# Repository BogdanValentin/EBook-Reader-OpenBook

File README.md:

# Proiect - OpenBook

## Diagrama Bloc

## Pasii de implementare
Am realizat in primul rand schema electrica propusa pe OCW. Apoi am realizat board-ul avand grija prima data sa tai placa dupa dimensiunile precizate. Am pus componentele pe placa incercand sa urmez designul propus. Am pus cele 2 planuri de masa si am rutat firele. Am creat modelele 3D pt placa, baterie si ecran si le-am asamblat in produsul finit.

## Probleme & decizii luate
Senzorul BME688 nu se afla in biblioteca ci BME680 asa ca l-am folosit pe acela. Apar mai multe erori la conectarea firelor GND to GND, am inteles ca mai multi se confrunta cu aceasta problema asa ca am lasat asa. Mufa USB creaza o eroare Board Outline Clearance care, la fel, am inteles ca este una comuna.

## Bill of Materials (BOM)

| Componenta                           | Link de Achizitie           | Datasheet                                                  |
|--------------------------------------|--------------------------------------------|------------------------------------------------------------|
| **USB C connector**                  | [Link](https://ro.mouser.com/ProductDetail/GCT/USB4110-GF-A?qs=KUoIvG%2F9IlYiZvIXQjyJeA%3D%3D&utm_id=6470900573&utm_source=google&utm_medium=cpc&utm_marketing_tactic=emeacorp&gad_source=1&gclid=EAIaIQobChMIw8-8kMWjjAMVcheiAx1TPQ31EAAYAiAAEgLwovD_BwE)                 | [Datasheet](https://ro.mouser.com/datasheet/2/837/GCT_USB4110_Product_Drawing___20k_cycles-3455479.pdf)                                             |
| **ESD Protection**                   | [Link](https://ro.mouser.com/ProductDetail/STMicroelectronics/USBLC6-2SC6Y?qs=gNDSiZmRJS%2FOgDexvXkdow%3D%3D&utm_id=6470900573&utm_source=google&utm_medium=cpc&utm_marketing_tactic=emeacorp&gad_source=1&gclid=EAIaIQobChMI0PCv18SjjAMVl1qRBR1ivRIGEAAYASAAEgKdf_D_BwE)                   | [Datasheet](https://ro.mouser.com/datasheet/2/389/usblc6_2sc6y-1852505.pdf)                                             |
| **LDO Voltage Regulator**            | [Link](https://ro.mouser.com/ProductDetail/Torex-Semiconductor/XC6220A331MR-G?qs=AsjdqWjXhJ8ZSWznL1J0gg%3D%3D&utm_id=6470900573&utm_source=google&utm_medium=cpc&utm_marketing_tactic=emeacorp&gad_source=1&gclid=EAIaIQobChMIyO-xwcSjjAMVwxeiAx0qMg1NEAAYASAAEgLqI_D_BwE)                   | [Datasheet](https://ro.mouser.com/datasheet/2/760/xc6220-3371556.pdf)                                             |
| **SD Card**                          | [Link](https://store.comet.srl.ro/Catalogue/Product/43497/?mark=2)                   | [Datasheet](https://www.attend.com.tw/data/download/file/112A-TAAR-R03.rar)                                             |
| **ESP32 C6**                         | [Link](https://ro.mouser.com/ProductDetail/Espressif-Systems/ESP32-C6?qs=Imq1NPwxi75noDtUpuVuWw%3D%3D&srsltid=AfmBOopGsscg6owTrNYpzSD_A6PeAhrd-8P7Q2gDTU-QmgxBLIUltlA7)                   | [Datasheet](https://ro.mouser.com/datasheet/2/891/esp32_c6_datasheet_en-3304070.pdf)                                             |
| **Li-Po Battery Charging Controller**| [Link](https://ro.mouser.com/ProductDetail/Microchip-Technology/MCP73831-2ATI-MC?qs=hH%252BOa0VZEiCb32ZvHkqhBQ%3D%3D&utm_id=20109199409&utm_source=google&utm_medium=cpc&utm_marketing_tactic=emeacorp&gad_source=1&gclid=EAIaIQobChMIwvChgMajjAMVxRCiAx3PNB47EAAYASAAEgIkZPD_BwE)                   | [Datasheet](https://ro.mouser.com/datasheet/2/268/MCP73831_Family_Data_Sheet_DS20001984H-3441711.pdf)                                             |                                            |
| **E-Paper Drive Circuit**            | [Link](https://ro.mouser.com/ProductDetail/Vishay-Semiconductors/SI1308EDL-T1-GE3?qs=bX1%252BNvsK%2FBramh9tgpOaEw%3D%3D&srsltid=AfmBOop7VB2nsZ4y3AQijBvo753QWrx9w51296dR8UjRlpwp_qg7iivF)                   | [Datasheet](https://www.vishay.com/doc?63399)                                             |
| **E-Paper Display Header**           | [Link](https://ro.mouser.com/ProductDetail/Hirose-Connector/FH34SRJ-24S-0.5SH99?qs=vcbW%252B4%252BSTIpKBl5ap9J8Fw%3D%3D)                   | [Datasheet](https://ro.mouser.com/datasheet/2/185/FH34SRJ_24S_0_5SH_99__CL0580_1255_6_99_2DDrawing_0-1615044.pdf)                                             |
| **EPD Power**                        | [Link](https://ro.mouser.com/ProductDetail/Diodes-Incorporated/DMG2305UX-7?qs=L1DZKBg7t5F%2FNBHrjfxC%252Bg%3D%3D)                   | [Datasheet](https://www.diodes.com/assets/Datasheets/DMG2305UX.pdf)                                             |
| **Environmental Sensor BME688**      | [Link](https://ro.mouser.com/ProductDetail/Bosch-Sensortec/BME688?qs=IS%252B4QmGtzzqQoVDscqwx3A%3D%3D)                   | [Datasheet](https://ro.mouser.com/datasheet/2/783/bst_bme688_fl000-2307034.pdf)                                             |
| **Voltage Supervisor**               | [Link](https://ro.mouser.com/ProductDetail/ROHM-Semiconductor/BD5229G-TR?qs=4kLU8WoGk0vvnhrrYwdszw%3D%3D&srsltid=AfmBOoohF8UhLJmEpguPyHuoa_qfrAg1xACnmLecyTKeAsNQaT9m0ZF5)                   | [Datasheet](https://fscdn.rohm.com/en/products/databook/datasheet/ic/power/voltage_detector/bd52xxg-e.pdf)                                             |
| **Battery Charge Level**             | [Link](https://ro.mouser.com/ProductDetail/Analog-Devices-Maxim-Integrated/MAX17048G+T10?qs=D7PJwyCwLAoGnnn8jEPRBQ%3D%3D&srsltid=AfmBOooZpxDFB0Ef_1d_Z6ZaAY3DUJrF2tjhVNvrkbPhjCJpjsk7k4Qx)                   | [Datasheet](https://ro.mouser.com/datasheet/2/609/MAX17048_MAX17049-3469099.pdf)                                             |
| **RTC Module DS3231SN**              | [Link](https://ro.mouser.com/ProductDetail/Analog-Devices-Maxim-Integrated/DS3231SNTR?qs=1eQvB6Dk1vhN%252BEOl3KU%252Bjw%3D%3D)                   | [Datasheet](https://ro.mouser.com/datasheet/2/609/DS3231-3421123.pdf)                                             |                                            |                                            |
| **SPI ESD Protection Lines**         | [Link](https://ro.mouser.com/ProductDetail/Littelfuse/PGB1010603MR?qs=gu7KAQ731URLg4GSnNNN7Q%3D%3D)                   | [Datasheet](https://www.littelfuse.com/assetdocs/pulseguard-esd-suppressors-pgb1-datasheet?assetguid=8a337998-d54d-466b-be4e-dc5bcd1f9321)                                             |
| **External NORFlash 64MB**           | [Link](https://ro.mouser.com/ProductDetail/Winbond/W25Q512JVEIQ?qs=l7cgNqFNU1jw6svr3at6tA%3D%3D&srsltid=AfmBOooYdTG4zpB4g9XFVQog2As1CX3DBItEO5x_Lv8uh1fPEpwC9MRH)                   | [Datasheet](https://ro.mouser.com/datasheet/2/949/Winbond_W25Q512JV_Datasheet-3240039.pdf)                                             |

---

## 3. Descrierea Functionalitatii Hardware

## Componente Folosite:

1. **USB C connector & ESD protection**  
2. **LDO Voltage Regulator**  
3. **SD card**  
4. **ESP32 C6**  
5. **Li-Po Battery Charging Controller**  
6. **Display Type Selector**  
7. **E-Paper Drive Circuit**  
8. **E-Paper Display Header**  
9. **EPD Power**  
10. **Environmental Sensor BME688**  
11. **Voltage Supervisor + Reset & Boot/IO Button**  
12. **Battery ChargeLevel**  
13. **RTC Module DS3231SN**  
14. **Qwiic/Stemma QT**  
15. **Test Pads**  
16. **SPI ESD Protection Lines**  
17. **External NORFlash 64MB**

---

## 4. ESP32-C6 Pini

| Componenta                          | Pini ESP32       | Rol     |
|-------------------------------------|---------------------|-------------|
| **E-Paper Display**                 | SPI (MISO, MOSI, CLK, CS) | Afisare |
| **BME688**                          | I2C (SDA, SCL)      | Senzor multirol |
| **RTC DS3231SN**                    | I2C (SDA, SCL)      | Ceas / Temporizare  |
| **Li-Po Battery Controller**        | GPIO  | incarcare   |
| **SD Card**                         | SPI (MISO, MOSI, CLK, CS) | Stocare date |
| **Qwiic/Stemma QT**                 | I2C                  | -  |

---

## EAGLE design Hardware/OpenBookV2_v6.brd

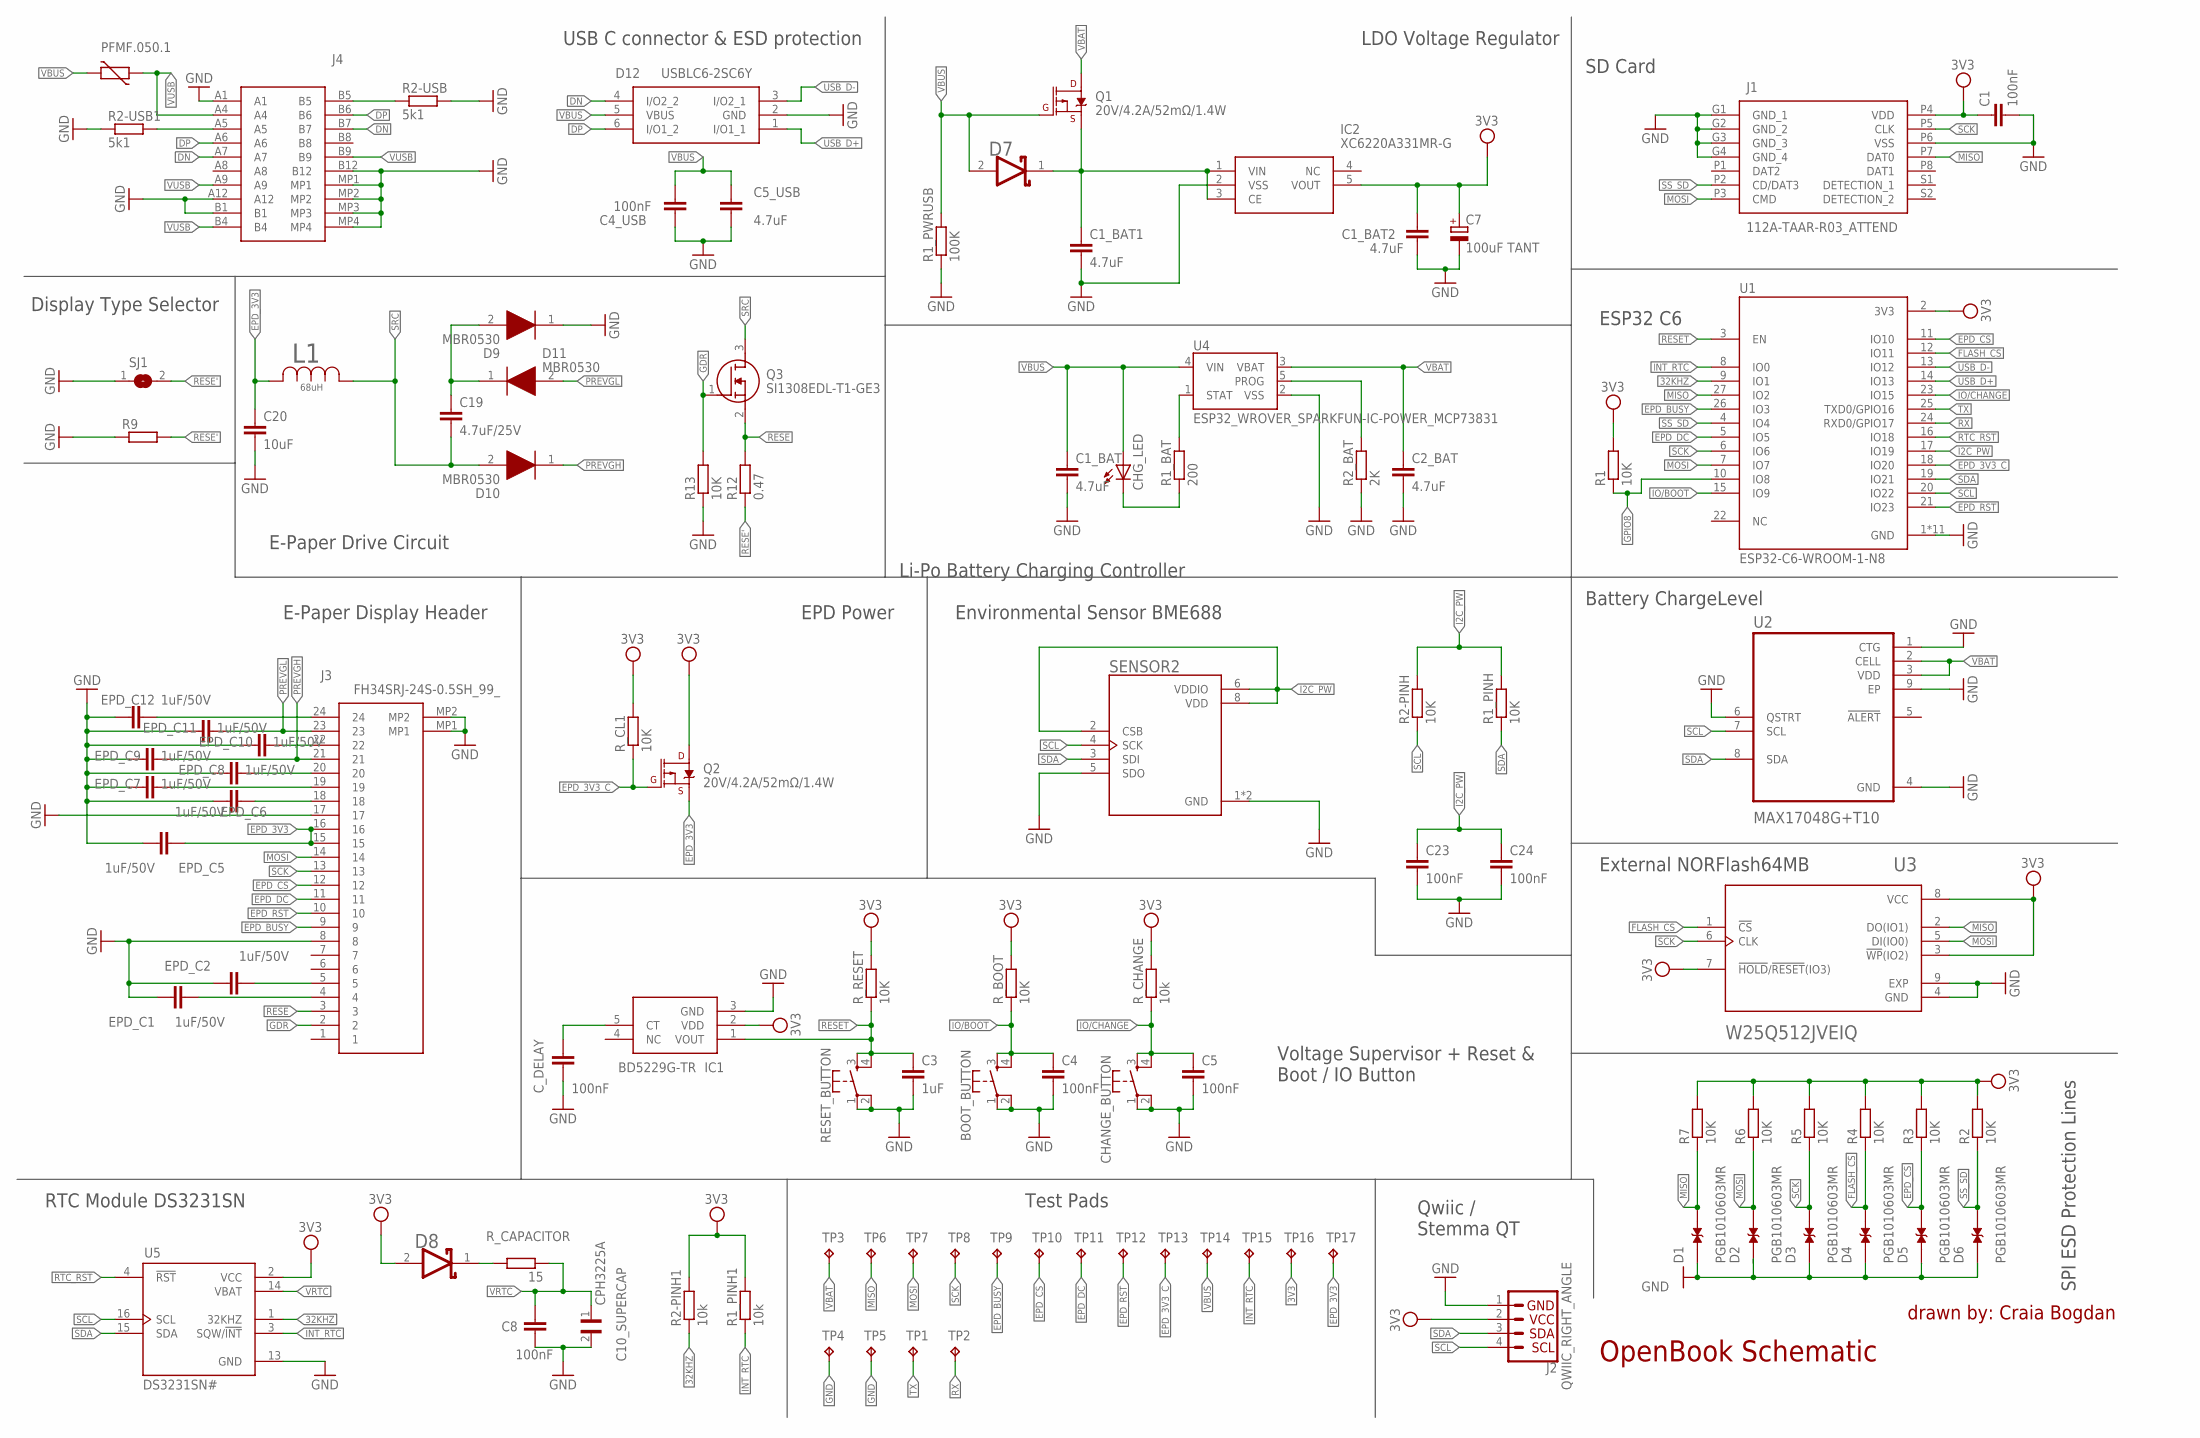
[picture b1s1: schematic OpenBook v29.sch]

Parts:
BOOT_BUTTON: BUTTON_CUSYOMV1; MYBUTTON
C1, C4, C4_USB, C5, C8, C23, C24: 100nF; EAGLE-LTSPICE_C0402
C1_BAT, C1_BAT1, C1_BAT2, C2_BAT, C5_USB: 4.7uF; EAGLE-LTSPICE_C0402
C3: 1uF; EAGLE-LTSPICE_C0402
C7: 100uF TANT; RCL_CT3528
C10_SUPERCAP: CPH3225A; CAPCP3225X100N
C19: 4.7uF/25V; EAGLE-LTSPICE_C0402
C20: 10uF; EAGLE-LTSPICE_C0402
CHANGE_BUTTON: BUTTON_CUSYOMV1; MYBUTTON
CHG_LED: ADAFRUIT_LEDCHIP-LED0603; ADAFRUIT_CHIP-LED0603
C_DELAY: 100nF; EAGLE-LTSPICE_C0402
D1, D2, D3, D4, D5, D6: PGB1010603MR; DIOC1608X36N
D7, D8: ESP32_WROVER_AVX---SD0805S020S1R0_AVX_SD0805S020S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; ESP32_WROVER_AVX---SD0805S020S1R0_AVX_SD0805S020S1R0_0
D9, D10, D11: MBR0530; SOD3716X135N
D12: USBLC6-2SC6Y; SOT95P280X145-6N
EPD_C1, EPD_C2, EPD_C5, EPD_C6, EPD_C7, EPD_C8, EPD_C9, EPD_C10, EPD_C11, EPD_C12: 1uF/50V; EAGLE-LTSPICE_C0402
IC1: BD5229G-TR; SOT95P280X125-5N
IC2: XC6220A331MR-G; SOT95P280X120-5N
J1: 112A-TAAR-R03_ATTEND; 112ATAARR03ATTEND
J2: QWIIC_RIGHT_ANGLE; JST04_1MM_RA
J3: FH34SRJ-24S-0.5SH_99_; FH34SRJ24S05SH99
J4: SAMACSYS_PARTS_USB4110-GF-A; SAMACSYS_PARTS_USB4110GFA
L1: 68uH; IND_4828-WE-TPC_WRE
PFMF.050.1: ESP32C6_VARISTORCN1812; ESP32C6_VARISTOR_CT/CN1812
Q1, Q2: 20V/4.2A/52mΩ/1.4W; ESP32_WROVER_SPARKFUN-DISCRETESEMI_SOT23-3
Q3: SI1308EDL-T1-GE3; SOT65P210X110-3N
R1, R1_PINH, R2, R2-PINH, R3, R4, R5, R6, R7, R13: 10K; ESP32_WROVER_EAGLE-LTSPICE_R0402
R1_BAT: 200; ESP32_WROVER_EAGLE-LTSPICE_R0402
R1_PINH1, R2-PINH1: 10k; ESP32_WROVER_EAGLE-LTSPICE_R0402
R1_PWRUSB: 100K; ESP32_WROVER_EAGLE-LTSPICE_R0402
R2-USB, R2-USB1: 5k1; ESP32_WROVER_EAGLE-LTSPICE_R0402
R2_BAT: 2K; ESP32_WROVER_EAGLE-LTSPICE_R0402
R9: ESP32_WROVER_EAGLE-LTSPICE_RR0402; ESP32_WROVER_EAGLE-LTSPICE_R0402
R12: 0.47; ESP32_WROVER_EAGLE-LTSPICE_R0402
RESET_BUTTON: BUTTON_CUSYOMV1; MYBUTTON
R_BOOT: 10K; ESP32_WROVER_EAGLE-LTSPICE_R0402
R_CAPACITOR: 15; ESP32_WROVER_EAGLE-LTSPICE_R0402
R_CHANGE: 10k; ESP32_WROVER_EAGLE-LTSPICE_R0402
R_CL1: 10K; ESP32_WROVER_EAGLE-LTSPICE_R0402
R_RESET: 10K; ESP32_WROVER_EAGLE-LTSPICE_R0402
SENSOR2: ESP32_WROVER_BME680_BME680; ESP32_WROVER_BME680_PSON80P300X300X100-8N
SJ1: SJ
TP1, TP2, TP3, TP4, TP5, TP6, TP7, TP8, TP9, TP10, TP11, TP12, TP13, TP14, TP15, TP16, TP17: TPTP20R; TP20R
U1: ESP32-C6-WROOM-1-N8; XCVR_ESP32-C6-WROOM-1-N8
U2: MAX17048G+T10; SON50P200X200X80-9N
U3: W25Q512JVEIQ; SON127P600X800X80-9N
U4: ESP32_WROVER_SPARKFUN-IC-POWER_MCP73831; ESP32_WROVER_SPARKFUN-IC-POWER_SOT23-5
U5: DS3231SN#; SOIC127P1032X265-16N

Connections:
3V3: C1.1, C1_BAT2.1, C7.+, D8.2 (ANODE), IC1.2 (VDD), IC2.5 (VOUT), J1.P4 (VDD), J2.2, Q2.3 (D), R1.2, R1_PINH1.2, R2.2, R2-PINH1.2, R3.2, R4.2, R5.2, R6.2, R7.2, R_BOOT.2, R_CHANGE.2, R_CL1.2, R_RESET.2, TP16.TP, U1.2 (3V3), U3.3 (!WP!(IO2)), U3.7 (!HOLD!/!RESET!(IO3)), U3.8 (VCC), U5.2 (VCC)
32KHZ: R2-PINH1.1, U1.9 (IO1), U5.1 (32KHZ)
DN: D12.4 (I/O2_2), J4.A7, J4.B7
DP: D12.6 (I/O1_2), J4.A6, J4.B6
EPD_3V3: C20.1, EPD_C5.2, J3.15, J3.16, L1.2, Q2.2 (S), TP17.TP
EPD_3V3_C: Q2.1 (G), R_CL1.1, TP13.TP, U1.18 (IO20)
EPD_BUSY: J3.9, TP9.TP, U1.26 (IO3)
EPD_CS: D5.2, J3.12, R3.1, TP10.TP, U1.11 (IO10)
EPD_DC: J3.11, TP11.TP, U1.5 (IO5)
EPD_RST: J3.10, TP12.TP, U1.21 (IO23)
FLASH_CS: D4.2, R4.1, U1.12 (IO11), U3.1 (!CS)
GDR: J3.2, Q3.1 (G), R13.2
GND: BOOT_BUTTON.1, BOOT_BUTTON.2, C1.2, C1_BAT.2, C1_BAT1.2, C1_BAT2.2, C2_BAT.2, C3.2, C4.2, C4_USB.2, C5.2, C5_USB.2, C7.-, C8.2, C10_SUPERCAP.2, C20.2, C23.2, C24.2, CHANGE_BUTTON.1, CHANGE_BUTTON.2, C_DELAY.2, D1.1, D2.1, D3.1, D4.1, D5.1, D6.1, D9.1 (K), D12.2 (GND), EPD_C1.1, EPD_C2.1, EPD_C5.1, EPD_C6.1, EPD_C7.1, EPD_C8.1, EPD_C9.1, EPD_C10.1, EPD_C11.1, EPD_C12.1, IC1.3 (GND), IC2.2 (VSS), J1.G1 (GND_1), J1.G2 (GND_2), J1.G3 (GND_3), J1.G4 (GND_4), J1.P6 (VSS), J2.1, J3.8, J3.17, J3.MP1, J3.MP2, J4.A1, J4.A12, J4.B1, J4.B12, J4.MP1, J4.MP2, J4.MP3, J4.MP4, R1_PWRUSB.1, R2-USB.2, R2-USB1.1, R2_BAT.1, R9.1, R13.1, RESET_BUTTON.1, RESET_BUTTON.2, SENSOR2.1 (GND), SENSOR2.5 (SDO), SENSOR2.7 (GND), SJ1.1, TP4.TP, TP5.TP, U1.1 (GND), U1.28 (GND), U1.29_1 (GND), U1.29_2 (GND), U1.29_3 (GND), U1.29_4 (GND), U1.29_5 (GND), U1.29_6 (GND), U1.29_7 (GND), U1.29_8 (GND), U1.29_9 (GND), U2.1 (CTG), U2.4 (GND), U2.6 (QSTRT), U2.9 (EP), U3.4 (GND), U3.9 (EXP), U4.2 (VSS), U5.13 (GND)
GPIO8: R1.1, U1.10 (IO8)
I2C_PW: C23.1, C24.1, R1_PINH.2, R2-PINH.2, SENSOR2.2 (CSB), SENSOR2.6 (VDDIO), SENSOR2.8 (VDD), U1.17 (IO19)
INT_RTC: R1_PINH1.1, TP15.TP, U1.8 (IO0), U5.3 (SQW/!INT)
IO/BOOT: BOOT_BUTTON.3, BOOT_BUTTON.4, C4.1, R_BOOT.1, U1.15 (IO9)
IO/CHANGE: C5.1, CHANGE_BUTTON.3, CHANGE_BUTTON.4, R_CHANGE.1, U1.23 (IO15)
MISO: D1.2, J1.P7 (DAT0), R7.1, TP6.TP, U1.27 (IO2), U3.2 (DO(IO1))
MOSI: D2.2, J1.P3 (CMD), J3.14, R6.1, TP7.TP, U1.7 (IO7), U3.5 (DI(IO0))
unnamed: C_DELAY.1, IC1.5 (CT)
unnamed: C1_BAT1.1, D7.1 (CATHODE), IC2.1 (VIN), IC2.3 (CE), Q1.2 (S)
unnamed: CHG_LED.C, R1_BAT.1
unnamed: R1_BAT.2, U4.1 (STAT)
unnamed: R2_BAT.2, U4.5 (PROG)
unnamed: D8.1 (CATHODE), R_CAPACITOR.1
unnamed: C19.1, D9.2 (A), D11.1 (K)
unnamed: J4.A5, R2-USB1.2
unnamed: J4.B5, R2-USB.1
unnamed: EPD_C2.2, J3.5
unnamed: EPD_C1.2, J3.4
unnamed: EPD_C6.2, J3.18
unnamed: EPD_C8.2, J3.20
unnamed: EPD_C10.2, J3.22
unnamed: EPD_C7.2, J3.19
unnamed: EPD_C12.2, J3.24
PREVGH: D10.1 (K), EPD_C9.2, J3.21
PREVGL: D11.2 (A), EPD_C11.2, J3.23
RESE: J3.3, Q3.2 (S), R12.2
RESE': R9.2, R12.1, SJ1.2
RESET: C3.1, IC1.1 (VOUT), RESET_BUTTON.3, RESET_BUTTON.4, R_RESET.1, U1.3 (EN)
RTC_RST: U1.16 (IO18), U5.4 (!RST)
RX: TP2.TP, U1.24 (RXD0/GPIO17)
SCK: D3.2, J1.P5 (CLK), J3.13, R5.1, TP8.TP, U1.6 (IO6), U3.6 (CLK)
SCL: J2.4, R2-PINH.1, SENSOR2.4 (SCK), U1.20 (IO22), U2.7 (SCL), U5.16 (SCL)
SDA: J2.3, R1_PINH.1, SENSOR2.3 (SDI), U1.19 (IO21), U2.8 (SDA), U5.15 (SDA)
SRC: C19.2, D10.2 (A), L1.1, Q3.3 (D)
SS_SD: D6.2, J1.P2 (CD/DAT3), R2.1, U1.4 (IO4)
TX: TP1.TP, U1.25 (TXD0/GPIO16)
USB_D+: D12.1 (I/O1_1), U1.14 (IO13)
USB_D-: D12.3 (I/O2_1), U1.13 (IO12)
VBAT: C2_BAT.1, Q1.3 (D), TP3.TP, U2.2 (CELL), U2.3 (VDD), U4.3 (VBAT)
VBUS: C1_BAT.1, C4_USB.1, C5_USB.1, CHG_LED.A, D7.2 (ANODE), D12.5 (VBUS), PFMF.050.1.2, Q1.1 (G), R1_PWRUSB.2, TP14.TP, U4.4 (VIN)
VRTC: C8.1, C10_SUPERCAP.1, R_CAPACITOR.2, U5.14 (VBAT)
VUSB: J4.A4, J4.A9, J4.B4, J4.B9, PFMF.050.1.1

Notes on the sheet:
USB C connector & ESD protection
LDO Voltage Regulator
SD Card
ESP32 C6
Li-Po Battery Charging Controller
E-Paper Drive Circuit
Display Type Selector
E-Paper Display Header
EPD Power
Environmental Sensor BME688
Voltage Supervisor + Reset & Boot / IO Button
Battery ChargeLevel
External NORFlash64MB
SPI ESD Protection Lines
Qwiic / Stemma QT
Test Pads
RTC Module DS3231SN
drawn by: Craia Bogdan
OpenBook Schematic

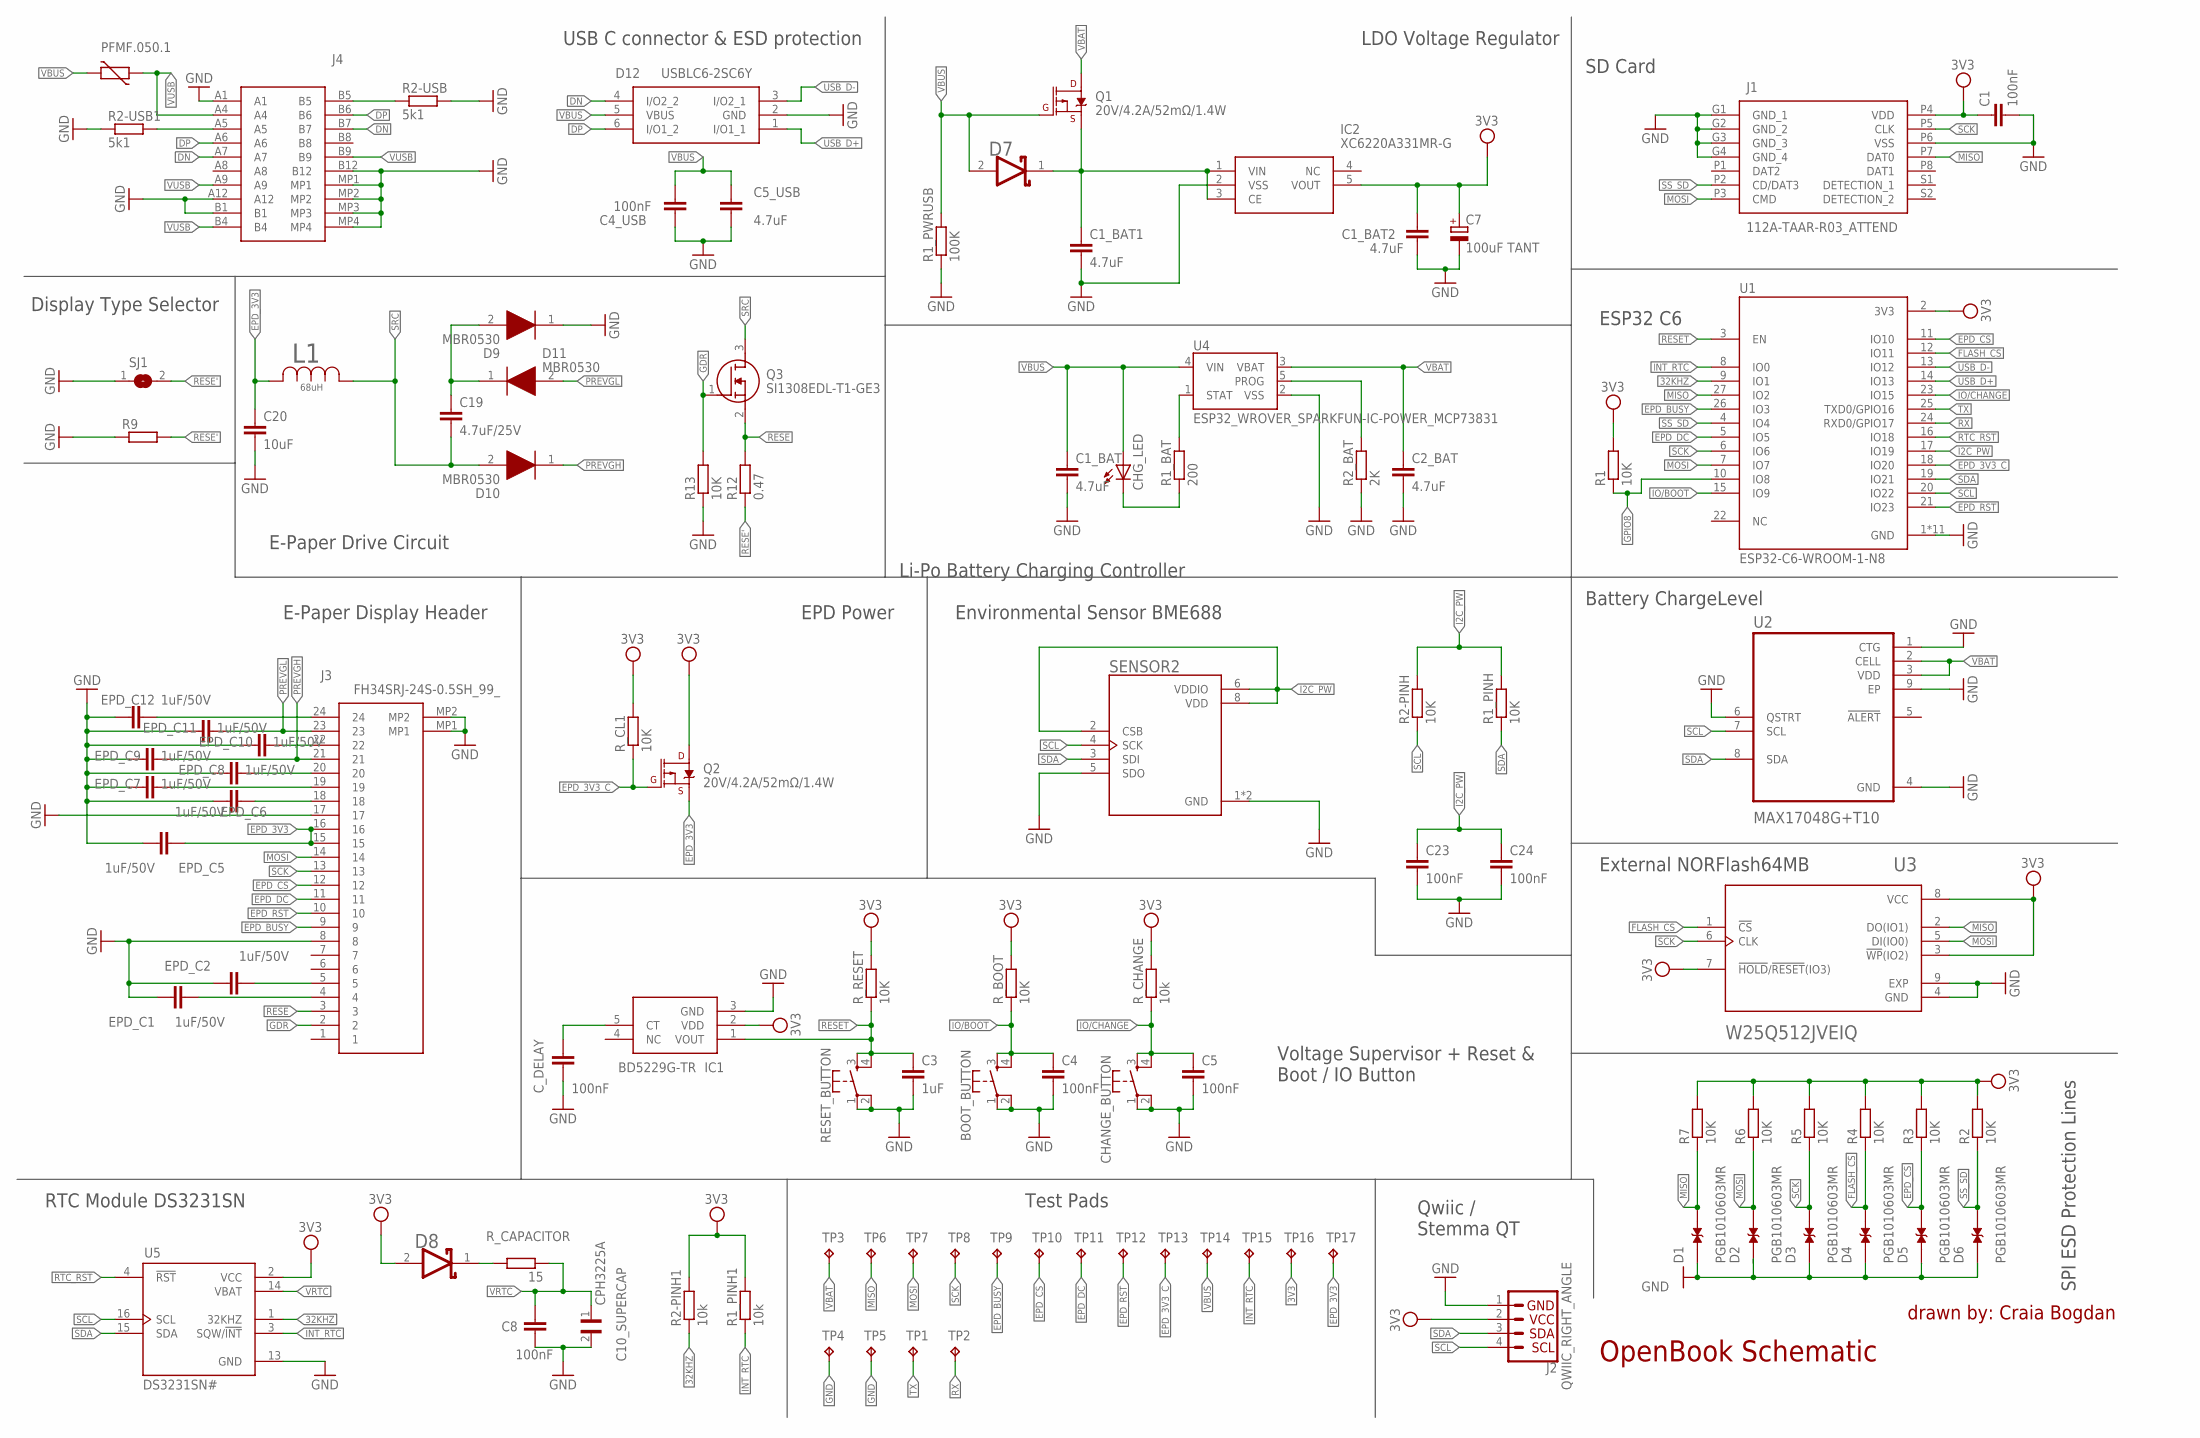
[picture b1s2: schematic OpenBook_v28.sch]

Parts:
BOOT_BUTTON: BUTTON_CUSYOMV1; MYBUTTON
C1, C4, C4_USB, C5, C8, C23, C24: 100nF; EAGLE-LTSPICE_C0402
C1_BAT, C1_BAT1, C1_BAT2, C2_BAT, C5_USB: 4.7uF; EAGLE-LTSPICE_C0402
C3: 1uF; EAGLE-LTSPICE_C0402
C7: 100uF TANT; RCL_CT3528
C10_SUPERCAP: CPH3225A; CAPCP3225X100N
C19: 4.7uF/25V; EAGLE-LTSPICE_C0402
C20: 10uF; EAGLE-LTSPICE_C0402
CHANGE_BUTTON: BUTTON_CUSYOMV1; MYBUTTON
CHG_LED: ADAFRUIT_LEDCHIP-LED0603; ADAFRUIT_CHIP-LED0603
C_DELAY: 100nF; EAGLE-LTSPICE_C0402
D1, D2, D3, D4, D5, D6: PGB1010603MR; DIOC1608X36N
D7, D8: ESP32_WROVER_AVX---SD0805S020S1R0_AVX_SD0805S020S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; ESP32_WROVER_AVX---SD0805S020S1R0_AVX_SD0805S020S1R0_0
D9, D10, D11: MBR0530; SOD3716X135N
D12: USBLC6-2SC6Y; SOT95P280X145-6N
EPD_C1, EPD_C2, EPD_C5, EPD_C6, EPD_C7, EPD_C8, EPD_C9, EPD_C10, EPD_C11, EPD_C12: 1uF/50V; EAGLE-LTSPICE_C0402
IC1: BD5229G-TR; SOT95P280X125-5N
IC2: XC6220A331MR-G; SOT95P280X120-5N
J1: 112A-TAAR-R03_ATTEND; 112ATAARR03ATTEND
J2: QWIIC_RIGHT_ANGLE; JST04_1MM_RA
J3: FH34SRJ-24S-0.5SH_99_; FH34SRJ24S05SH99
J4: SAMACSYS_PARTS_USB4110-GF-A; SAMACSYS_PARTS_USB4110GFA
L1: 68uH; IND_4828-WE-TPC_WRE
PFMF.050.1: ESP32C6_VARISTORCN1812; ESP32C6_VARISTOR_CT/CN1812
Q1, Q2: 20V/4.2A/52mΩ/1.4W; ESP32_WROVER_SPARKFUN-DISCRETESEMI_SOT23-3
Q3: SI1308EDL-T1-GE3; SOT65P210X110-3N
R1, R1_PINH, R2, R2-PINH, R3, R4, R5, R6, R7, R13: 10K; ESP32_WROVER_EAGLE-LTSPICE_R0402
R1_BAT: 200; ESP32_WROVER_EAGLE-LTSPICE_R0402
R1_PINH1, R2-PINH1: 10k; ESP32_WROVER_EAGLE-LTSPICE_R0402
R1_PWRUSB: 100K; ESP32_WROVER_EAGLE-LTSPICE_R0402
R2-USB, R2-USB1: 5k1; ESP32_WROVER_EAGLE-LTSPICE_R0402
R2_BAT: 2K; ESP32_WROVER_EAGLE-LTSPICE_R0402
R9: ESP32_WROVER_EAGLE-LTSPICE_RR0402; ESP32_WROVER_EAGLE-LTSPICE_R0402
R12: 0.47; ESP32_WROVER_EAGLE-LTSPICE_R0402
RESET_BUTTON: BUTTON_CUSYOMV1; MYBUTTON
R_BOOT: 10K; ESP32_WROVER_EAGLE-LTSPICE_R0402
R_CAPACITOR: 15; ESP32_WROVER_EAGLE-LTSPICE_R0402
R_CHANGE: 10k; ESP32_WROVER_EAGLE-LTSPICE_R0402
R_CL1: 10K; ESP32_WROVER_EAGLE-LTSPICE_R0402
R_RESET: 10K; ESP32_WROVER_EAGLE-LTSPICE_R0402
SENSOR2: ESP32_WROVER_BME680_BME680; ESP32_WROVER_BME680_PSON80P300X300X100-8N
SJ1: SJ
TP1, TP2, TP3, TP4, TP5, TP6, TP7, TP8, TP9, TP10, TP11, TP12, TP13, TP14, TP15, TP16, TP17: TPTP20R; TP20R
U1: ESP32-C6-WROOM-1-N8; XCVR_ESP32-C6-WROOM-1-N8
U2: MAX17048G+T10; SON50P200X200X80-9N
U3: W25Q512JVEIQ; SON127P600X800X80-9N
U4: ESP32_WROVER_SPARKFUN-IC-POWER_MCP73831; ESP32_WROVER_SPARKFUN-IC-POWER_SOT23-5
U5: DS3231SN#; SOIC127P1032X265-16N

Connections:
3V3: C1.1, C1_BAT2.1, C7.+, D8.2 (ANODE), IC1.2 (VDD), IC2.5 (VOUT), J1.P4 (VDD), J2.2, Q2.3 (D), R1.2, R1_PINH1.2, R2.2, R2-PINH1.2, R3.2, R4.2, R5.2, R6.2, R7.2, R_BOOT.2, R_CHANGE.2, R_CL1.2, R_RESET.2, TP16.TP, U1.2 (3V3), U3.3 (!WP!(IO2)), U3.7 (!HOLD!/!RESET!(IO3)), U3.8 (VCC), U5.2 (VCC)
32KHZ: R2-PINH1.1, U1.9 (IO1), U5.1 (32KHZ)
DN: D12.4 (I/O2_2), J4.A7, J4.B7
DP: D12.6 (I/O1_2), J4.A6, J4.B6
EPD_3V3: C20.1, EPD_C5.2, J3.15, J3.16, L1.2, Q2.2 (S), TP17.TP
EPD_3V3_C: Q2.1 (G), R_CL1.1, TP13.TP, U1.18 (IO20)
EPD_BUSY: J3.9, TP9.TP, U1.26 (IO3)
EPD_CS: D5.2, J3.12, R3.1, TP10.TP, U1.11 (IO10)
EPD_DC: J3.11, TP11.TP, U1.5 (IO5)
EPD_RST: J3.10, TP12.TP, U1.21 (IO23)
FLASH_CS: D4.2, R4.1, U1.12 (IO11), U3.1 (!CS)
GDR: J3.2, Q3.1 (G), R13.2
GND: BOOT_BUTTON.1, BOOT_BUTTON.2, C1.2, C1_BAT.2, C1_BAT1.2, C1_BAT2.2, C2_BAT.2, C3.2, C4.2, C4_USB.2, C5.2, C5_USB.2, C7.-, C8.2, C10_SUPERCAP.2, C20.2, C23.2, C24.2, CHANGE_BUTTON.1, CHANGE_BUTTON.2, C_DELAY.2, D1.1, D2.1, D3.1, D4.1, D5.1, D6.1, D9.1 (K), D12.2 (GND), EPD_C1.1, EPD_C2.1, EPD_C5.1, EPD_C6.1, EPD_C7.1, EPD_C8.1, EPD_C9.1, EPD_C10.1, EPD_C11.1, EPD_C12.1, IC1.3 (GND), IC2.2 (VSS), J1.G1 (GND_1), J1.G2 (GND_2), J1.G3 (GND_3), J1.G4 (GND_4), J1.P6 (VSS), J2.1, J3.8, J3.17, J3.MP1, J3.MP2, J4.A1, J4.A12, J4.B1, J4.B12, J4.MP1, J4.MP2, J4.MP3, J4.MP4, R1_PWRUSB.1, R2-USB.2, R2-USB1.1, R2_BAT.1, R9.1, R13.1, RESET_BUTTON.1, RESET_BUTTON.2, SENSOR2.1 (GND), SENSOR2.5 (SDO), SENSOR2.7 (GND), SJ1.1, TP4.TP, TP5.TP, U1.1 (GND), U1.28 (GND), U1.29_1 (GND), U1.29_2 (GND), U1.29_3 (GND), U1.29_4 (GND), U1.29_5 (GND), U1.29_6 (GND), U1.29_7 (GND), U1.29_8 (GND), U1.29_9 (GND), U2.1 (CTG), U2.4 (GND), U2.6 (QSTRT), U2.9 (EP), U3.4 (GND), U3.9 (EXP), U4.2 (VSS), U5.13 (GND)
GPIO8: R1.1, U1.10 (IO8)
I2C_PW: C23.1, C24.1, R1_PINH.2, R2-PINH.2, SENSOR2.2 (CSB), SENSOR2.6 (VDDIO), SENSOR2.8 (VDD), U1.17 (IO19)
INT_RTC: R1_PINH1.1, TP15.TP, U1.8 (IO0), U5.3 (SQW/!INT)
IO/BOOT: BOOT_BUTTON.3, BOOT_BUTTON.4, C4.1, R_BOOT.1, U1.15 (IO9)
IO/CHANGE: C5.1, CHANGE_BUTTON.3, CHANGE_BUTTON.4, R_CHANGE.1, U1.23 (IO15)
MISO: D1.2, J1.P7 (DAT0), R7.1, TP6.TP, U1.27 (IO2), U3.2 (DO(IO1))
MOSI: D2.2, J1.P3 (CMD), J3.14, R6.1, TP7.TP, U1.7 (IO7), U3.5 (DI(IO0))
unnamed: C_DELAY.1, IC1.5 (CT)
unnamed: C1_BAT1.1, D7.1 (CATHODE), IC2.1 (VIN), IC2.3 (CE), Q1.2 (S)
unnamed: CHG_LED.C, R1_BAT.1
unnamed: R1_BAT.2, U4.1 (STAT)
unnamed: R2_BAT.2, U4.5 (PROG)
unnamed: D8.1 (CATHODE), R_CAPACITOR.1
unnamed: C19.1, D9.2 (A), D11.1 (K)
unnamed: J4.A5, R2-USB1.2
unnamed: J4.B5, R2-USB.1
unnamed: EPD_C2.2, J3.5
unnamed: EPD_C1.2, J3.4
unnamed: EPD_C6.2, J3.18
unnamed: EPD_C8.2, J3.20
unnamed: EPD_C10.2, J3.22
unnamed: EPD_C7.2, J3.19
unnamed: EPD_C12.2, J3.24
PREVGH: D10.1 (K), EPD_C9.2, J3.21
PREVGL: D11.2 (A), EPD_C11.2, J3.23
RESE: J3.3, Q3.2 (S), R12.2
RESE': R9.2, R12.1, SJ1.2
RESET: C3.1, IC1.1 (VOUT), RESET_BUTTON.3, RESET_BUTTON.4, R_RESET.1, U1.3 (EN)
RTC_RST: U1.16 (IO18), U5.4 (!RST)
RX: TP2.TP, U1.24 (RXD0/GPIO17)
SCK: D3.2, J1.P5 (CLK), J3.13, R5.1, TP8.TP, U1.6 (IO6), U3.6 (CLK)
SCL: J2.4, R2-PINH.1, SENSOR2.4 (SCK), U1.20 (IO22), U2.7 (SCL), U5.16 (SCL)
SDA: J2.3, R1_PINH.1, SENSOR2.3 (SDI), U1.19 (IO21), U2.8 (SDA), U5.15 (SDA)
SRC: C19.2, D10.2 (A), L1.1, Q3.3 (D)
SS_SD: D6.2, J1.P2 (CD/DAT3), R2.1, U1.4 (IO4)
TX: TP1.TP, U1.25 (TXD0/GPIO16)
USB_D+: D12.1 (I/O1_1), U1.14 (IO13)
USB_D-: D12.3 (I/O2_1), U1.13 (IO12)
VBAT: C2_BAT.1, Q1.3 (D), TP3.TP, U2.2 (CELL), U2.3 (VDD), U4.3 (VBAT)
VBUS: C1_BAT.1, C4_USB.1, C5_USB.1, CHG_LED.A, D7.2 (ANODE), D12.5 (VBUS), PFMF.050.1.2, Q1.1 (G), R1_PWRUSB.2, TP14.TP, U4.4 (VIN)
VRTC: C8.1, C10_SUPERCAP.1, R_CAPACITOR.2, U5.14 (VBAT)
VUSB: J4.A4, J4.A9, J4.B4, J4.B9, PFMF.050.1.1

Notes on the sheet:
USB C connector & ESD protection
LDO Voltage Regulator
SD Card
ESP32 C6
Li-Po Battery Charging Controller
E-Paper Drive Circuit
Display Type Selector
E-Paper Display Header
EPD Power
Environmental Sensor BME688
Voltage Supervisor + Reset & Boot / IO Button
Battery ChargeLevel
External NORFlash64MB
SPI ESD Protection Lines
Qwiic / Stemma QT
Test Pads
RTC Module DS3231SN
drawn by: Craia Bogdan
OpenBook Schematic

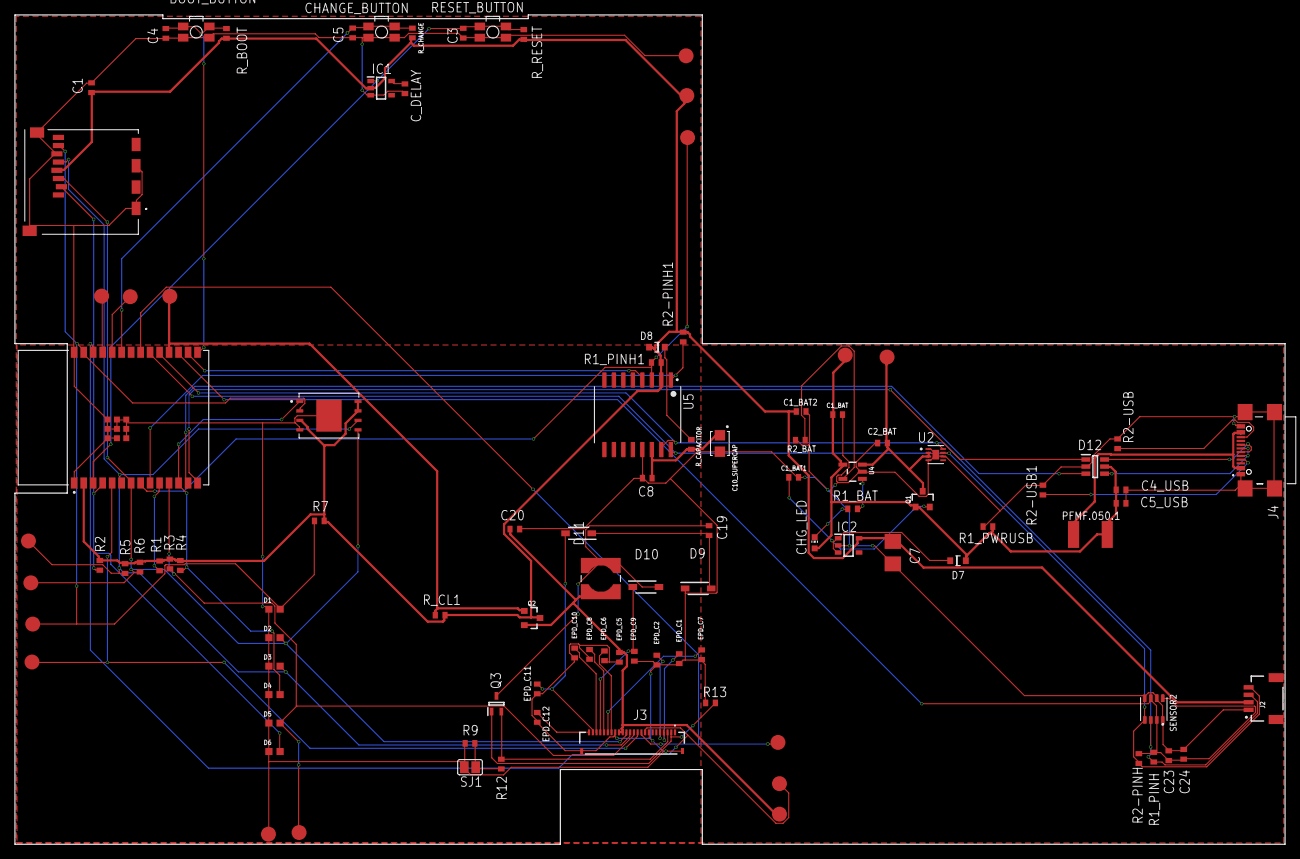
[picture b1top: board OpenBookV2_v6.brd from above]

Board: 2 copper layers, 170.0 x 111.0 mm, 103 parts (0 on the bottom side), 55 nets.

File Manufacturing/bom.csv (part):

Qty,Value,Device,Package,Parts,Description,ARROW_PART_NUMBER,ARROW_PRICE-STOCK,AVAILABILITY,CENTROID_NOT_SPECIFIED,CHECK_PRICES,COPYRIGHT,DATASHEET,DESCRIPTION,DIGIKEY_DESCRIPTION,DIGIKEY_PART_NUMBER,HEIGHT,LEAD_FREE,MANUFACTURER_NAME,MANUFACTURER_PART_NUMBER,MF,MFR_NAME,MOUSER_PART_NUMBER,MOUSER_PRICE-STOCK,MOUSER_TESTING_PART_NUMBER,MOUSER_TESTING_PRICE-STOCK,MP,MPN,PACKAGE,POPULARITY,PREFIX,PRICE,PROD_ID,PURCHASE-URL,ROHS,SNAPEDA_LINK,SPICEMODEL,SPICEPREFIX,TEMPERATURE_RANGE_HIGH,TEMPERATURE_RANGE_LOW,TP_SIGNAL_NAME,VALUE
1,,ADAFRUIT_LEDCHIP-LED0603,ADAFRUIT_CHIP-LED0603,CHG_LED,LED,,,,,,,,,,,,,,,,,,,,,,,,,,,,,,,,,,,,
3,,BUTTON_CUSYOMV1,MYBUTTON,"BOOT_BUTTON, CHANGE_BUTTON, RESET_BUTTON",,,,,,,,,,,,,,,,,,,,,,,,,,,,,,,,,,,,,
1,,ESP32_WROVER_EAGLE-LTSPICE_RR0402,ESP32_WROVER_EAGLE-LTSPICE_R0402,R9,"RESISTOR, European symbol",,,,,,,,,,,,,,,,,,,,,,,,,,,,,,,NONE,R,,,,
1,,SJ,SJ,SJ1,"SMD solder JUMPER",,,,,,,,,,,,,,,,,,,,,,,,3,,,,,,,,,,,,
1,0.47,ESP32_WROVER_EAGLE-LTSPICE_RR0402,ESP32_WROVER_EAGLE-LTSPICE_R0402,R12,"RESISTOR, European symbol",,,,,,,,,,,,,,,,,,,,,,,,,,,,,,,NONE,R,,,,
1,100K,ESP32_WROVER_EAGLE-LTSPICE_RR0402,ESP32_WROVER_EAGLE-LTSPICE_R0402,R1_PWRUSB,"RESISTOR, European symbol",,,,,,,,,,,,,,,,,,,,,,,,,,,,,,,NONE,R,,,,
8,100nF,EAGLE-LTSPICE_CC0402,EAGLE-LTSPICE_C0402,"C1, C4, C4_USB, C5, C8, C23, C24, C_DELAY","CAPACITOR, European symbol",,,,,,,,,,,,,,,,,,,,,,,,,,,,,,,NONE,C,,,,
1,"100uF TANT",RCL_CPOL-EUCT3528,RCL_CT3528,C7,"POLARIZED CAPACITOR, European symbol",,,,,,,,,,,,,,,,,,,,,,,,0,,,,,,,,C,,,,
13,10K,ESP32_WROVER_EAGLE-LTSPICE_RR0402,ESP32_WROVER_EAGLE-LTSPICE_R0402,"R1, R1_PINH, R2, R2-PINH, R3, R4, R5, R6, R7, R13, R_BOOT, R_CL1, R_RESET","RESISTOR, European symbol",,,,,,,,,,,,,,,,,,,,,,,,,,,,,,,NONE,R,,,,
3,10k,ESP32_WROVER_EAGLE-LTSPICE_RR0402,ESP32_WROVER_EAGLE-LTSPICE_R0402,"R1_PINH1, R2-PINH1, R_CHANGE","RESISTOR, European symbol",,,,,,,,,,,,,,,,,,,,,,,,,,,,,,,NONE,R,,,,
1,10uF,EAGLE-LTSPICE_CC0402,EAGLE-LTSPICE_C0402,C20,"CAPACITOR, European symbol",,,,,,,,,,,,,,,,,,,,,,,,,,,,,,,NONE,C,,,,
1,112A-TAAR-R03_ATTEND,112A-TAAR-R03_ATTEND,112ATAARR03ATTEND,J1,"Micro SD Card Socket, Push-Push Type, Top Mount, SMT, H=1.83mm, 10u",,,,,,,,"Micro SD Card Socket"," Push-Push Type"," Top Mount"," SMT"," H=1.83mm"," 10u",,,1.9mm,,ATTEND,"112A-TAAR-R03 ATTEND",,,,,,,,,,,,,,,,,
1,15,ESP32_WROVER_EAGLE-LTSPICE_RR0402,ESP32_WROVER_EAGLE-LTSPICE_R0402,R_CAPACITOR,"RESISTOR, European symbol",,,,,,,,,,,,,,,,,,,,,,,,,,,,,,,NONE,R,,,,
1,1uF,EAGLE-LTSPICE_CC0402,EAGLE-LTSPICE_C0402,C3,"CAPACITOR, European symbol",,,,,,,,,,,,,,,,,,,,,,,,,,,,,,,NONE,C,,,,
10,1uF/50V,EAGLE-LTSPICE_CC0402,EAGLE-LTSPICE_C0402,"EPD_C1, EPD_C2, EPD_C5, EPD_C6, EPD_C7, EPD_C8, EPD_C9, EPD_C10, EPD_C11, EPD_C12","CAPACITOR, European symbol",,,,,,,,,,,,,,,,,,,,,,,,,,,,,,,NONE,C,,,,
1,200,ESP32_WROVER_EAGLE-LTSPICE_RR0402,ESP32_WROVER_EAGLE-LTSPICE_R0402,R1_BAT,"RESISTOR, European symbol",,,,,,,,,,,,,,,,,,,,,,,,,,,,,,,NONE,R,,,,
2,20V/4.2A/52mO/1.4W,ESP32_WROVER_SPARKFUN-DISCRETESEMI_MOSFET_PCH-DMG2305UX-7,ESP32_WROVER_SPARKFUN-DISCRETESEMI_SOT23-3,"Q1, Q2","P-channel MOSFETs",,,,,,,,,,,,,,,,,,,,,,,,,,,TRAN-14388,,,,,,,,,20V/4.2A/52mO/1.4W
1,2K,ESP32_WROVER_EAGLE-LTSPICE_RR0402,ESP32_WROVER_EAGLE-LTSPICE_R0402,R2_BAT,"RESISTOR, European symbol",,,,,,,,,,,,,,,,,,,,,,,,,,,,,,,NONE,R,,,,
4,4.7uF,EAGLE-LTSPICE_CC0402,EAGLE-LTSPICE_C0402,"C1_BAT, C1_BAT1, C1_BAT2, C5_USB","CAPACITOR, European symbol",,,,,,,,,,,,,,,,,,,,,,,,,,,,,,,NONE,C,,,,
1,"4.7uF ",EAGLE-LTSPICE_CC0402,EAGLE-LTSPICE_C0402,C2_BAT,"CAPACITOR, European symbol",,,,,,,,,,,,,,,,,,,,,,,,,,,,,,,NONE,C,,,,
1,4.7uF/25V,EAGLE-LTSPICE_CC0402,EAGLE-LTSPICE_C0402,C19,"CAPACITOR, European symbol",,,,,,,,,,,,,,,,,,,,,,,,,,,,,,,NONE,C,,,,
2,5k1,ESP32_WROVER_EAGLE-LTSPICE_RR0402,ESP32_WROVER_EAGLE-LTSPICE_R0402,"R2-USB, R2-USB1","RESISTOR, European symbol",,,,,,,,,,,,,,,,,,,,,,,,,,,,,,,NONE,R,,,,
1,68uH,744043680IND_4828-WE-TPC_WRE,IND_4828-WE-TPC_WRE,L1,,,,,,,"Copyright (C) 2024 Ultra Librarian. All rights reserved.",,,,,,,,744043680,,"Wurth Electronics",,,,,,,,,,,,,,,,,,,,
1,BD5229G-TR,BD5229G-TR,SOT95P280X125-5N,IC1,"Voltage Detector with Adjustable Delay Time: CMOS processes are utilized to develop high precision, low current consumption CMOS reset ICs that allow arbitrary setting of the delay time. The extensive lineup includes both Nch Open Drain and CMOS output types in a wide range of detection voltages (from 2.3V to 6.0V, in 0.1V steps), enabling selection of the ideal solution based on customer requirements. In addition, the entire series is of course both lead-free and RoHS-compliant.",,,,,,,,"Voltage Detector with Adjustable Delay Time: CMOS processes are utilized to develop high precision"," low current consumption CMOS reset ICs that allow arbitrary setting of the delay time. The extensive lineup includes both Nch Open Drain and CMOS output types in a wide range of detection voltages (from 2.3V to 6.0V"," in 0.1V steps)"," enabling selection of the ideal solution based on customer requirements. In addition"," the entire series is of course both lead-free and RoHS-compliant.",,,1.25mm,,"ROHM Semiconductor",BD5229G-TR,,,755-BD5229G-TR,https://www.mouser.co.uk/ProductDetail/ROHM-Semiconductor/BD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,,,,,,,,,,,,,,
1,CPH3225A,CPH3225A,CAPCP3225X100N,C10_SUPERCAP,"Cap 0.011F 3.3V 1210 Flat Check availability",,,"Not in stock",,https://www.snapeda.com/parts/CPH3225A/Seiko+Instruments/vie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,,," 11 mF (EDLC) Supercapacitor 3.3 V 1210 (3225 Metric) - - ",,,,,,,"Seiko Instruments",,,,,,CPH3225A,,"1210 Seiko",,,None,,"https://www.snapeda.com/api/url_track_click_mouser/?unipart_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 Instruments&part_name=CPH3225A&search_term=None",,https://www.snapeda.com/parts/CPH3225A/Seiko+Instruments/vie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,,,,,,
1,DS3231SN#,DS3231SN#,SOIC127P1032X265-16N,U5,"Real Time Clock Serial 16-Pin SOIC W T/R     Check availability",,,"In Stock",,https://www.snapeda.com/parts/DS3231SN%23/Analog+Devices/vie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,,," Extremely Accurate I²C-Integrated RTC/TCXO/Crystal ",,,,,,,"Analog Devices",,,,,,DS3231SN#,,"SOIC-16 Maxim",,,None,,"https://www.snapeda.com/api/url_track_click_mouser/?unipart_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 Devices&part_name=DS3231SN#&search_term=None",,https://www.snapeda.com/parts/DS3231SN%23/Analog+Devices/vie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,,,,,,
1,ESP32-C6-WROOM-1-N8,ESP32-C6-WROOM-1-N8,XCVR_ESP32-C6-WROOM-1-N8,U1,"Check availability",,,"In Stock",,https://www.snapeda.com/parts/ESP32-C6-WROOM-1-N8/Espressif+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,,," Multiprotocol Modules ESP32-C6 module"," Wi-Fi 6 in 2.4 GHz band"," Bluetooth 5"," Zigbee 3.0 and Thread. ESP34-WROOM Compatible - ENGINEERING SAMPLE ",,,,,,,"Espressif Systems",,,,,,ESP32-C6-WROOM-1-N8,,None,,,None,,,,https://www.snapeda.com/parts/ESP32-C6-WROOM-1-N8/Espressif+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,,,
1,ESP32C6_VARISTORCN1812,ESP32C6_VARISTORCN1812,ESP32C6_VARISTOR_CT/CN1812,PFMF.050.1,VARISTOR,,,,,,,,,,,,,,,,,,,,,,,,0,,,,,,,,,,,,
2,ESP32_WROVER_AVX---SD0805S020S1R0_AVX_SD0805S020S1R0_0_0AVX_SD0805S020S1R0_0_0,ESP32_WROVER_AVX---SD0805S020S1R0_AVX_SD0805S020S1R0_0_0AVX_SD0805S020S1R0_0_0,ESP32_WROVER_AVX---SD0805S020S1R0_AVX_SD0805S020S1R0_0,"D7, D8","Schottky Barrier Rectifier Diode",,,,No,,,http://datasheets.avx.com/schottky.pdf,,"DIODE SCHOTTKY 20V 1A 0805",478-7800-1-ND,,yes,,,AVX,,581-SD0805S020S1R0,,,,,,"0805 (2012 metric)",,D,,,,yes,,,,+125°C,-55°C,,
1,ESP32_WROVER_BME680_BME680,ESP32_WROVER_BME680_BME680,ESP32_WROVER_BME680_PSON80P300X300X100-8N,SENSOR2,"Integrated Environmental Unit",,,Unavailable,,,,," Integrated Environmental Unit ",,,,,,,"Bosch Sensortec",,,,,,BME680,,"LGA-8 Bosch Tools",,,None,,,,,,,,,,
1,ESP32_WROVER_SPARKFUN-IC-POWER_MCP73831,ESP32_WROVER_SPARKFUN-IC-POWER_MCP73831,ESP32_WROVER_SPARKFUN-IC-POWER_SOT23-5,U4,"MCP73831T Li-Ion, Li-Pol Controller",,,,,,,,,,,,,,,,,,,,,,,,,,,IC-09995,,,,,,,,,
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
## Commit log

2025-03-24 Create LICENSE
2025-03-27 added files
2025-04-03 updated design
2025-04-10 Modificare board

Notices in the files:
parts and their libraries:
DeskAssistant v19 v1: COPYRIGHT: Copyright (C) 2024 Ultra Librarian. All rights reserved.
